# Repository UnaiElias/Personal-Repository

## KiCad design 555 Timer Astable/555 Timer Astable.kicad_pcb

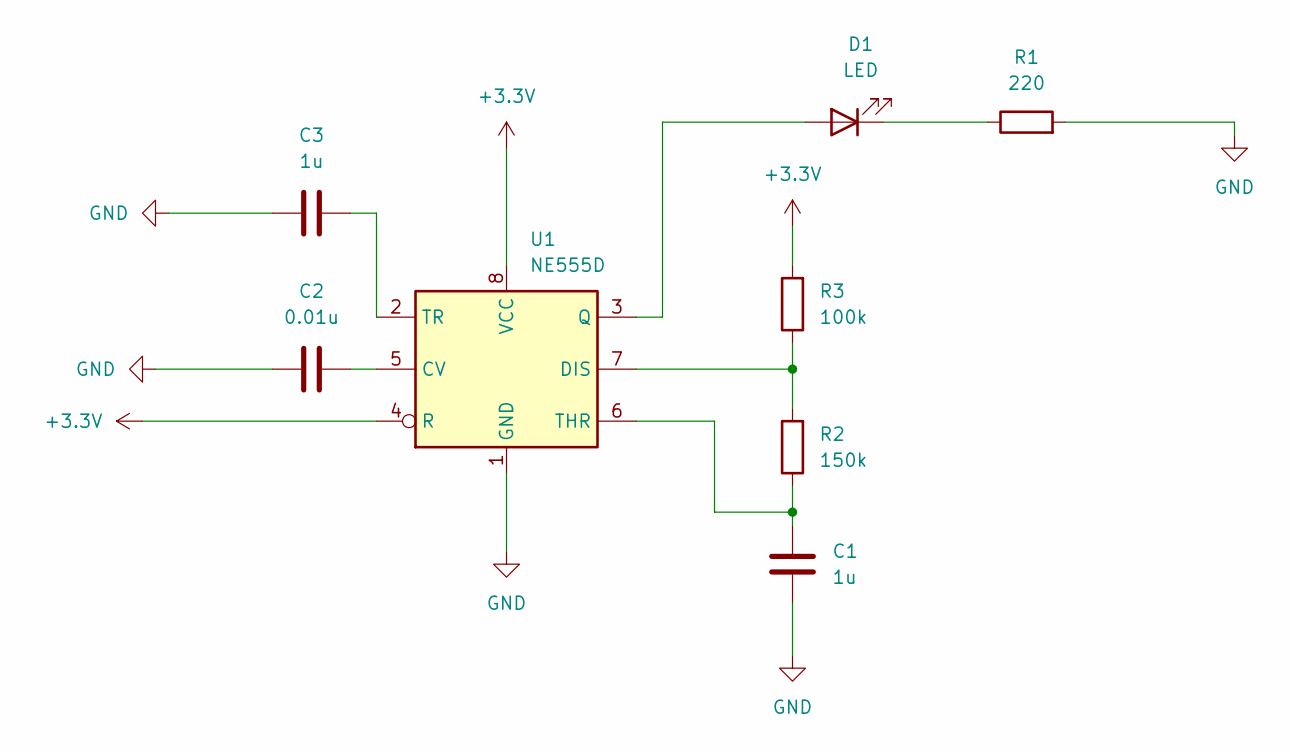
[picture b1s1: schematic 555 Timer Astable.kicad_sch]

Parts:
C1, C3: 1u; C_1812_4532Metric
C2: 0.01u; C_1812_4532Metric
D1: LED; LED_0603_1608Metric
R1: 220; R_0603_1608Metric
R2: 150k; R_0603_1608Metric
R3: 100k; R_0603_1608Metric
U1: NE555D; SOIC-8_3.9x4.9mm_P1.27mm

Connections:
+3.3V: R3.2, U1.4 (R), U1.8 (VCC)
GND: C1.2, C2.1, C3.1, R1.2, U1.1 (GND)
unnamed: D1.2 (A), U1.3 (Q)
unnamed: D1.1 (K), R1.1
unnamed: C2.2, U1.5 (CV)
unnamed: R2.2, R3.1, U1.7 (DIS)
unnamed: C1.1, R2.1, U1.6 (THR)
unnamed: C3.2, U1.2 (TR)

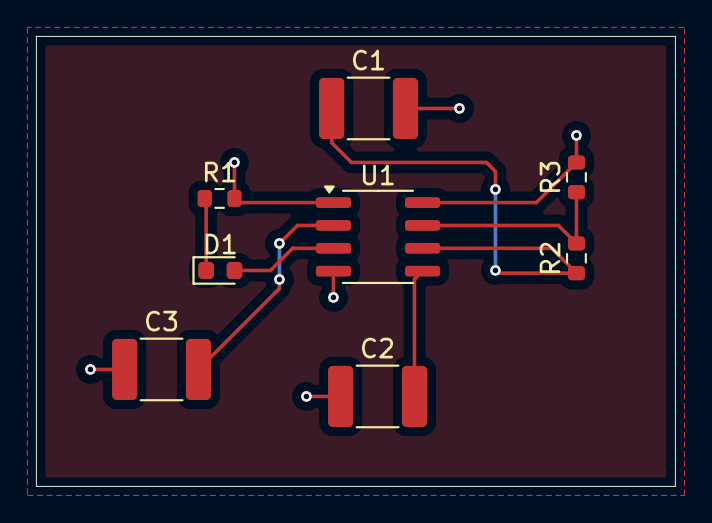
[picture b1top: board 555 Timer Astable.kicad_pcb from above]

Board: 4 copper layers, 35.5 x 25.0 mm, 8 parts (0 on the bottom side), 8 nets.

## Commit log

2024-09-24 Added KiCad 555 Astable Timer
